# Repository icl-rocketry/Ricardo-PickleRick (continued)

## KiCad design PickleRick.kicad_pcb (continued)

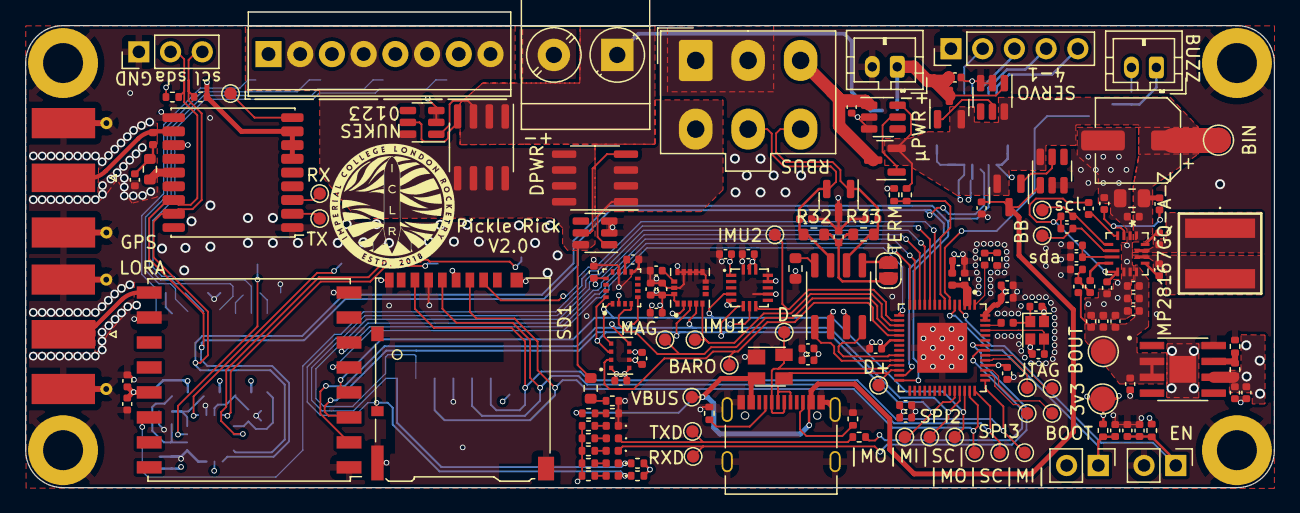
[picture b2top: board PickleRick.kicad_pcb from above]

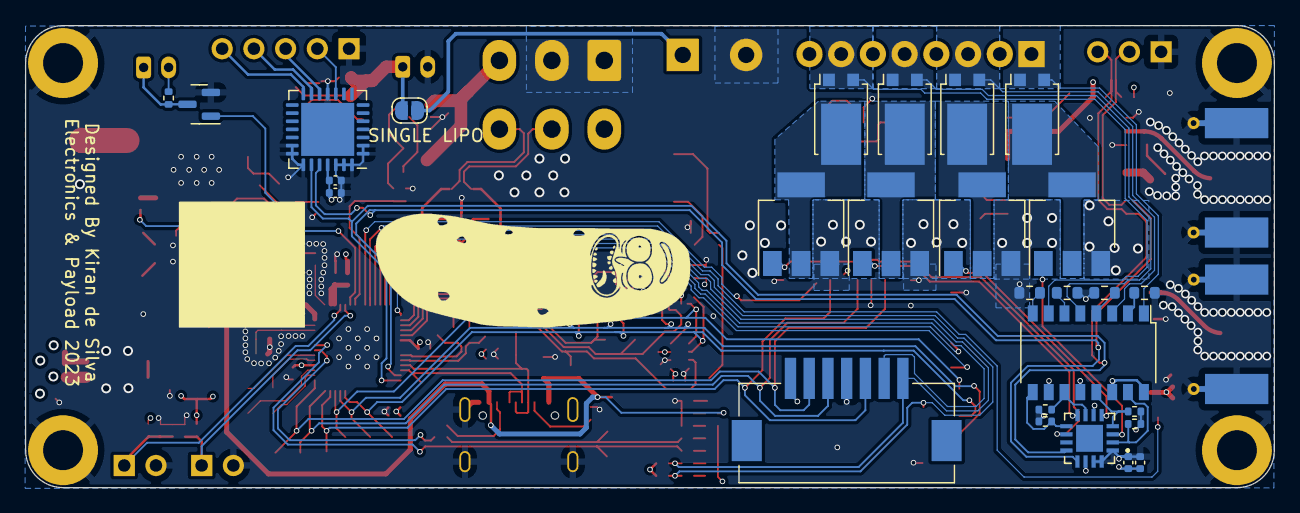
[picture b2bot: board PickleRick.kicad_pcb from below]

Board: 4 copper layers, 100.0 x 37.0 mm, 191 parts (27 on the bottom side), 116 nets.

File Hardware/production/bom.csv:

Designator,Footprint,Quantity,Value,LCSC Part #
"12VLED1, D24, D25, D26, D27",0402,5,RED_LED,
"BOOTJUMPER1, ENJUMPER1",PinHeader_1x02_P2.54mm_Vertical,2,Conn_01x02_Male,
"C1, C2, C28, C32, C6",0402,5,1uF,
"C10, C11, C12, C25, C29, C31, C34, C35, C37, C4, C41, C46, C58, C59, C7, C8, C9",0402,17,0.1uF,
"C13, C14",0402,2,11pF,
"C15, C16, C18, C20, C22, C39, C40, C50, C56",0402,9,100nF,
"C17, C19, C21, C27, C3, C45, C51, C55",0402,8,10uF,
C23,0402,1,0.47uF,
"C24, C49, C5",0402,3,10nF,
C26,0402,1,2.2uF,
"C30, C33",0402,2,22nF,
C36,0805,1,22uF,
C38,CP_Elec_6.3x9.9,1,100uF,
"C42, C43, C47, C48, C57",0402,5,22uF,
C44,0402,1,4.7uF,
C52,0402,1,47nF,
"D1, D13",0402,2,ORANGE_LED,
"D10, D7, D8, D9",TO-277B,4,D_Schottky,
D11,SOT-23,1,SM712_SOT23,
"D12, D20, D21, D22, D23, D3",0402,6,EMERALD_LED,
"D14, D15, D16, D17",SODFL3516X70N,4,S-102T,
D18,SOT-353_SC-70-5,1,~,
D19,RCLAMP3346PQTNT,1,RCLAMP3346PQTNT,
"D2, D4",0402,2,GREEN_LED,
D5,0402,1,BLUE_LED,
D6,SOT-143,1,SP0503BAHT,
E1,Spark_Gap,1,SparkGap,
"H1, H2, H3, H4",MountingHole_3.2mm_M3_DIN965_Pad,4,MountingHole_Pad,
IC1,SON65P300X300X100-9N-D,1,MIC5060YML-TR,
J1,Molex_Mini-Fit_Jr_5566-06A_2x03_P4.20mm_Vertical,1,RBUS,
"J10, J11",SMA_Molex_73251-1153_EdgeMount_Horizontal,2,Conn_Coaxial,
J12,PinHeader_1x03_P2.54mm_Vertical,1,Conn_01x03_Male,
J13,Molex_Nano-Fit_105313-xx03_1x03_P2.50mm_Horizontal,1,Conn_01x03_Pin,
J14,Molex_Pico-Clasp_202396-0707_1x07-1MP_P1.00mm_Horizontal,1,Conn_01x07_Socket,
J2,JST_PH_B2B-PH-K_1x02_P2.00mm_Vertical,1,Conn_01x02_Male,
J3,JAE_ST1W008S4TR2000,1,ST1W008S4TR2000,
J4,PinHeader_1x03_P2.54mm_Vertical,1,Conn_01x03_Pin,
J5,USB_C_Receptacle_Palconn_UTC16-G,1,USB_C_Receptacle_USB2.0,
J6,TerminalBlock_TE_282834-8_1x08_P2.54mm_Horizontal,1,Screw_Terminal_01x08,
J7,PinHeader_1x05_P2.54mm_Vertical,1,Conn_01x05_Male,
J8,TerminalBlock_Phoenix_MKDS-3-2-5.08_1x02_P5.08mm_Horizontal,1,DeployLipo,
J9,JST_PH_B2B-PH-K_1x02_P2.00mm_Vertical,1,UCLipo,
JP2,SolderJumper-2_P1.3mm_Open_RoundedPad1.0x1.5mm,1,SolderJumper_2_Open,
JP3,SmallerSolderJP,1,TermJP,
L1,0402,1,2.0nH,
L2,0402,1,20nH,
L3,MPLAL60504R7,1,MPL-AL6050-4R7,
L4,0402,1,27nH,
LS1,CMT052575SMTTR,1,CMT-0525-75-SMT-TR,
Q1,SOT-23,1,PMV20ENR,
"Q10, Q8, Q9",SOT-23,3,DMP3099L,
"Q11, Q12",SQS850ENT1_GE3,2,SQS141ELNW-T1_GE3,
"Q2, Q3, Q4, Q5, Q6",BSZ025N04LS,5,BSZ025N04LS,
"R1, R13, R24, R26, R29, R36, R43, R44, R46, R48, R6",0402,11,10K,
"R10, R2, R3, R38, R39, R4, R5, R7",0402,8,470,
R11,0402,1,1k,
"R12, R17, R18, R21, R22, R49, R50, R51",0402,8,120,
"R14, R15, R16",0402,3,5.1k,
R19,2512,1,2m,
"R20, R23",0402,2,10,
"R25, R45",0402,2,80k,
R27,0402,1,499k,
R28,0402,1,56k,
R30,0603,1,10,
R31,0603,1,0,
"R32, R33",0603,2,60,
"R34, R35",0402,2,2.2k,
R37,0402,1,37.4k,
R40,0402,1,806k,
R41,0402,1,430k,
R42,0402,1,143k,
"R47, R52, R53, R54",0402,4,220,
R8,0402,1,0,
R9,0402,1,499,
"TP10, TP11, TP13",TestPoint_Pad_D2.0mm,3,TestPoint,
TP15,TestPoint_Pad_D1.0mm,1,GPS_RESET,
"TP16, TP17, TP22, TP23, TP24, TP25, TP26, TP27, TP28, TP5, TP6, TP7, TP8, TP9",TestPoint_Pad_D1.0mm,14,TestPoint,
U1,QFN40P700X700X90-57N,1,ESP32-S3,
"U10, U14, U17, U22, U9",TSOT-23-6,5,LTC4412xS6,
U11,MP28167GQ-A-Z,1,MP28167GQ-A-Z,
U12,SOT-23-8,1,INA219AxDCN,
U16,SOIC127P599X175-9N,1,SC4215,
U19,ublox_MAX,1,MAX-M10S,
U2,XDCR_DPS310,1,DPS368,
U20,SOIC-8_3.9x4.9mm_P1.27mm,1,SN65HVD230,
U21,HOPERF_RFM9XW_SMD,1,RFM95W-868S2,
U3,SOP-16_4.4x10.4mm_P1.27mm,1,LTV-247,
U4,QFN65P400X400X100-17N,1,PCA9534RGVR,
U5,QFN-28-1EP_6x6mm_P0.65mm_EP4.25x4.25mm,1,PCA9685BS,
U6,QFN300X300X100-16N,1,H3LIS331DLTR,
U7,PQFN50P300X300X80-16N,1,ICM-20608-G,
U8,PQFN50P300X300X100-16N,1,MMC5983MA,
USBLED1,0402,1,WHITE_LED,
Y1,Crystal_SMD_2016-4Pin_2.0x1.6mm,1,R940000171,

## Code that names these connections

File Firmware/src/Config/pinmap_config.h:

#pragma once

namespace PinMap 
{
    //Buzzer
    static constexpr int Buzzer = 1;

    //LoRa
    static constexpr int LoraReset = 9;
    static constexpr int LoraCs = 10;
    static constexpr int LoraInt = 4;

    //VSPI
    static constexpr int V_SCLK = 37;
    static constexpr int V_MISO = 38;
    static constexpr int V_MOSI = 36;

    //HSPI
    static constexpr int H_MISO = 34;
    static constexpr int H_MOSI = 33;
    static constexpr int H_SCLK = 35;

    //Interial Sensors
    static constexpr int MagCs = 13;
    static constexpr int ImuCs_1 = 12;
    static constexpr int ImuCs_2 = 11;
    static constexpr int BaroCs = 14;
    static constexpr int PPS = 39;

    //gpio -> doubles as JTAG PINS
    static constexpr int GPIO0 = 40;
    static constexpr int GPIO1 = 41;
    static constexpr int GPIO2 = 42;

    //ABUS
    static constexpr int ABUS_RX = 48;
    static constexpr int ABUS_TX = 47;

    //I2C
    static constexpr int _SDA = 21;
    static constexpr int _SCL = 26;
    
    //SD Storage
    static constexpr int SdCs_1 = 8;
    static constexpr int SdCs_2 = 7;
    static constexpr int SdDet_1 = 5;
    static constexpr int SdDet_2 = 6;
  
    //CAN
    static constexpr int TxCan = 18;
    static constexpr int RxCan = 17;

    //VRail Sense
    // static constexpr int BattVolt = 2;
    static constexpr int LogicVolt = 2;
    static constexpr int DepVolt = 16;
    static constexpr int DepSwitch = 15;
    
    //PCA9634 Mapping 
    static constexpr int Ch0Fire = 1;
    static constexpr int Ch1Fire = 3;
    static constexpr int Ch2Fire = 5;
    static constexpr int Ch3Fire = 7;

    static constexpr int Ch0Cont = 0;
    static constexpr int Ch1Cont = 2;
    static constexpr int Ch2Cont = 4;
    static constexpr int Ch3Cont = 6;

    //PCA9685 Mapping
    static constexpr int servo0pin = 7;
    static constexpr int servo1pin = 8;
    static constexpr int servo2pin = 9;
    static constexpr int servo3pin = 10;

};

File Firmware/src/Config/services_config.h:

/**
 * @file services_config.h
 * @author Kiran de Silva (kd619@ic.ac.uk)
 * @brief Defintion of user defined services
 * @version 0.1
 * @date 2023-06-17
 * 
 * @copyright Copyright (c) 2023
 * 
 */
#pragma once

#include <stdint.h>


namespace Services{
    /**
     * @brief ID of user defined services NB start at 2, all ID's below 2 are reserved for default services found in 'rnp_networkmanager.h'
     * 
     */
    enum class ID:uint8_t{
        HITL = 3,
        DeploymentHandler = 4,
        EngineHandler = 5,
        EventHandler = 6,
        GuidedHandler = 7,
        Pyro0 = 10,
        Pyro1 = 11,
        Pyro2 = 12,
        Pyro3 = 13,
        Servo0 = 20,
        Servo1 = 21,
        Servo2 = 22,
        Servo3 = 23
    };

};

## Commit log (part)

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2022-02-14 added pickle rick
2022-02-15 Added LMR14050 buck converter to pickle rick
2022-03-01 Annotated schematic & done layout for buck converter
2022-03-20 first full layout of pickle complete
2022-03-22 pickle layed out
2022-03-28 pickle update
2022-03-28 removed some vias to conform to jlcpcb 100k holes per sqm
2022-03-28 pcikle
2022-03-28 changed autoprogrammer cap values
2022-04-01 final changes to pick rick
2022-04-07 switched vspi and hspi labels so they are consistent with documentation
2022-06-27 added i2c comms to mag class as mag seems to not work over spi, currently debugging this.
2022-07-05 migrated python_backend to its own repo, sperated flight controller code and groundstation gateway code
2022-11-27 working on v2
2022-12-12 v2 time
2022-12-23 first layout of s3
2023-01-01 Conitnued with v2, NB pinout of external sd card has changed!!! Chest needs to be updated before manufacturing!!!
2023-02-11 made more progress
2023-02-12 minor updates
2023-02-25 converted to kicad 7
2023-03-18 changed bb and power side
2023-03-31 some updates?
2023-04-10 did layout of buck kinda. 90% there
2023-04-10 initial layout complete
2023-04-15 almost done
2023-07-07 imagine fixing your DRC errors
2023-07-08 fixed some stuff
2023-07-21 new standardized directory setup
2023-07-26 added firmware
2023-07-26 renamed submodule;
2023-07-26 rewrote batttery class as voltage monitor
2023-07-27 converting sensors to new framework
2023-07-27 adding states to the mix
2023-07-28 more stuff done
2023-07-31 well it compiles...
2023-07-31 updated fixes to libricore
2023-08-06 added pinmap for pickle rick v2
2023-08-07 udpated ini
2023-08-08 added dps libary and writing wrapper for dps310
2023-08-08 fixing the arduino library, aka leave my spi bus alone
2023-08-10 dealing with the stupid baro
2023-08-11 fixed the dps310 driver
2023-08-11 fixed buzzer issues and removed serial print from mmc5983ma library
2023-08-12 fixed battery reading
2023-08-19 acceloremeter calibration
2023-08-19 Radio Setup Change
2023-08-22 swapped command ids for mag and high-g accel. Tested with hitl, seems to crash if hitl poll rate is too high
2023-08-28 mag axes flip
2023-08-28 mag axes correct inshaallah
2023-09-05 3D model directory
    Hopefully now if you configure paths in the 3d model section to your iclrhw 3d model directory, all 3d models should load
2023-09-05 black edition ordering stuff
2023-09-05 3D update
2023-09-06 pulled latest libriccore
2023-09-16 forgot to add some new variances
2023-09-21 updated to newest libriccore
2023-09-22 added log messages
2023-09-23 fixed bounds check bug
2023-09-23 added config loading
2023-09-23 fixed deadlock in storage stuff
2023-09-27 fixed no sd bug
2023-09-28 updated librnp to main
2023-09-28 updated librrc to main
2023-09-28 thanos class
2023-09-28 added thanos to engine handler
2023-09-28 updated librrc
2023-10-02 changed libriccore to master
2023-10-06 uh idk
2023-10-11 added per sensor config of axes, needs checking tho
2023-10-12 fixes
2023-10-12 updated lora radio
2023-12-03 set radio output to 20 dbm
2024-01-05 wrote pca class
2024-01-06 fires once, still need to fix things
2024-01-07 pyros are working
2024-01-08 doesnt really work
2024-01-09 updat
2024-01-10 added local_pyro functioanlity to engine handler and deployment handler
2024-01-10 moved network setup to system setup
2024-01-17 breaking api change on flight config json, events now REQUIRE an ID
2024-02-18 still issues with syncing post discovery
2024-02-18 libriccore update
2024-03-07 updated arduino
2024-03-12 fixed arduino lib issues
2024-03-16 updated submodule url
2024-03-16 some dead bugfix
2024-03-17 updated ini and added andus dead fix
2024-03-17 ficing stuff
2024-03-26 fixing more
2024-03-27 debugging radio
2024-04-13 identified bugs with how axis defnitions are taking place... madgwick filter seems to have a funky axis defnition aswell, need to investigate further. Fixed mag calibnrations not saving
2024-04-13 Modified madgwick to NED, reverted Kiran's axes changes on v3-DEV
2024-04-13 Set lora transmit power too 100mW
2024-04-13 Swapped lin accel and imu calibration
2024-04-14 Enabled json comments
2024-04-21 added event firendly names and documentation to event class
2024-04-21 type alias to librrc jsonconfighelper version to keep code modular and consistent
2024-04-21 removed unused helpers and replaced all references to the local jsonconfighelper to the impelmentation in librrc
2024-04-22 added a name paramter to events
2024-04-22 updated submodule
2024-04-22 finally fixed the dps310 always reporting intialized bug
2024-06-04 packet sending to chad
2024-06-04 The sendtest codes were added
2024-06-04 PID class
2024-06-04 Saved PID class
2024-06-07 gonna try to get acking of heartbeats to work
2024-06-08 added test
2024-06-15 Testing Gain matrix and updated sendTest
2024-06-21 radio test setup
2024-06-22 changed arduino-Lora to iclr fork
2024-07-02 added flight variables for various orinetaitons and tilt angle
2024-07-02 added configurable radio thru sd config file
2024-07-02 added anlge of nutation calculation
2024-07-02 added 10km ekf cut off for barometer
2024-07-03 Added (temporary) NVS radio config
2024-07-03 Fixed a submodule oopsie
2024-07-03 fixed bugs
2024-07-04 fixed for smores
2024-07-06 udated pca9534 driver to write shadows to i2c deivce on setupo
2024-07-20 updated librnp
2024-07-21 added new radio mode to try debug the radio driver
2024-07-22 v3 hardware start
2024-08-15 more hardware updates
2024-08-16 progress
2024-08-16 hardware update
2024-08-17 added cont and firing leds
2024-08-17 hardware complete
2024-08-17 updated antenna trace widths
2024-08-17 added planes
2024-08-17 fioxed keep out for efuse
2024-08-18 replaced efuse with ina219
2024-09-01 updated hardware with current limitng resistors on pwm outputs
2024-09-02 updated pickle firmware with new servo hal, finally enablign local servos on pickle!
2024-09-02 hardware updates
2024-09-02 slightly refactored event handler with a function map rather than long if statement
2024-09-04 added contiutiy detection in the event handler for switch based triggers
2024-09-20 added v3 pin map
2024-09-21 added hardware version enviomrents in pio rather than chip based enviroments as v3 has the smae mcu as v2
2024-10-01 added ereg commands to thanosR, added support for INA in pickle [WARNING] telemetry packet changed! NFET master swtich permantley on for now
2024-10-01 added bug fixes and ereg shutting on shutdown
2024-10-01 fxied can bus erase issue
2024-10-02 implemneted disarming of deployers and engines on a abort
2024-10-02 added log message
2024-10-02 routing table
2024-10-02 gss chad connected to the pi route
2024-10-02 kiran engine fixes
2024-10-02 fixed thanos r to prevent spamming of venting
2024-10-03 updataed thanos R to reset vent bools on disarm
2024-10-04 sd card log 32 bit overflow fix
2024-10-08 fixed bugs in thanosR impl
2024-10-09 updated commands to include an apogee override command for debugging
2024-10-09 added new songs
2024-10-09 routing table update
2024-10-11 implemented generic argument aciton in eventhanlder
2024-10-20 Updated submodule Firmware/lib/SdFat
2024-10-20 trying to fix submodule version de-sync
2024-10-21 post euroc push
2024-10-21 updated submodules
2024-10-22 copying old files from broken branch
2024-10-27 Auto stash before merge of "v3-DEV" and "origin/v3-DEV"
2024-11-01 Update .gitmodules
    to point to fork
2024-11-19 This works :)
    Pickle sending command packets to Chad for gimble control
2024-11-29 Added functions to find error and integral error
2024-11-29 commit before rebasing to update
2024-11-29 Current calibrate_impl() build, correction for serialize data
2024-12-03 Start working on interface
2024-12-03 Some more code
2024-12-07 scaffolded next stage of implementation
2024-12-10 Changes till Dec 10th
2024-12-10 fucked around and found out
2024-12-16 laptop exploded, recovered files from gimble working
2024-12-22 updated estimator rocket orientation with correct maths
2025-01-12 radio fully converted to continous receive
2025-01-12 updated submdou;es
2025-01-14 updated ledc api
2025-01-14 updated ini with new framework
2025-01-14 updated arduino to 3.1.1
2025-01-14 compiles on 5.3
2025-01-18 updated ring buffer implementation to use std::array for static memory alloc
2025-01-18 BREAKING CHANGE ublox max m8q no longer supported
2025-01-22 updated librricore to v4-dev
2025-02-06 Fixed outdated LEDC api call in TunezHandler
2025-02-11 cleaned up code
2025-02-13 Adding some 3d models
2025-02-14 Implemented initial GNC state machine
2025-02-14 Full v3 Pickle 3d model
2025-02-14 3d model was in the wrong place
2025-02-18 theoretically fixed orientation neu not ned
2025-02-22 Tweaked GNC state machine
2025-03-15 Added SMC.cpp and SMC.h which are copy of PID but included SMC control action
2025-03-15 fixed smc
2025-04-04 updated controller interaction with rest of code
2025-04-04 added landing sequence
2025-04-22 dragged some of v4 code into the repo (lowkey this branch is cooked)
2025-04-23 Deleted rogue .vscode folder
2025-05-17 python PID controller
2025-07-07 added reorientation thing but needs work
2025-07-07 updated timing comment
2025-07-07 Updated with Backstepping and Sliding mode controller (not working)
2025-07-09 tweaked implementation (still broken)
2025-07-09 working through estimator stuff (still not working)
2025-07-23 new set of gains
2025-07-26 Added AS7265X
2025-07-26 Updated telemetry packet
2025-08-02 tuning time!
2025-08-08 Shortened Telem Packet
2025-08-19 dirty implementation of rtk but working
2025-09-18 feat: Enabling FTS command by default
2025-10-13 updated networking table for pluto networking
2025-10-13 updated librrc with bugfix
2026-01-20 [jar24] feat : Implemented hitl package recieving and activation for the pickle rick board
2026-01-28 submodules
2026-03-31 prelim stuff
2026-04-02 removed arduino dps3xx package
2026-04-03 sensor drivers reformatted
2026-04-05 debugging ekf
2026-04-05 oreintation working!! need to decide whether to add in bias estimation or translation first
2026-04-06 removed madgwick
2026-04-06 position ekf implemented, still need tuning for better quality and less drift
2026-04-07 changed it again for increased accuracy of position
2026-04-10 changed a bunch of stuff but pushing so oli can use
2026-04-10 auto starting
2026-04-12 copied the changes over
2026-04-13 recalibrated servo angles
2026-04-19 quaternions no longer cooked
2026-04-23 added low pass filter to accelerometer and gyro
2026-04-25 EKF tuned, PD controller tuned, time to send
2026-04-29 Added Roll Control
2026-04-30 Added in thrust battery voltage scaling
2026-05-02 lidar implemented, first draft of position controller also implemented
2026-05-07 Sped up the EKF, made one timing file, added estimator SD card Logging
2026-05-07 added trapezoidal trajectory generation
2026-05-10 verified controller with testing, changed controller to NED
2026-05-12 Added safety features
2026-05-20 GPS velocity straight to ekf, fixed GPS bug where _pvt.valid stays true forever after the first byte
2026-05-20 custom throttle profile
2026-05-30 Added baseboard design v0
2026-06-02 Restore controlled IMU interface in schematic hierarchy
2026-06-02 Updated Baseboard design but with power supply problems
2026-06-02 Eliminated some errors, U505 still contains errors
2026-06-07 RTK added, not working, future me problem
2026-06-10 RTK implemented and working, now just changing gains and sending it
2026-06-13 RTK time stamping, now running at 20hz
2026-06-14 added retrodiction for the RTK measurements, see https://tinyurl.com/retrodiction for more info
2026-06-14 sped up ekf, sped up GPS read
2026-06-16 Added GPS retrodiction, changed retrodiction timing to be based on PPS interrupt, fixed UTC to GPS time bug, added serial print debug config file
2026-06-16 GNC demo? completed it m8
2026-06-16 centre of mass tuned
2026-06-23 added autopilot landing, added multiple trajectories, tuned controller, made magnetometer only affect the heading (roll), not pitch and yaw
2026-06-24 cleaned up schematic and bom
2026-06-24 updated resistors w cap footprints
